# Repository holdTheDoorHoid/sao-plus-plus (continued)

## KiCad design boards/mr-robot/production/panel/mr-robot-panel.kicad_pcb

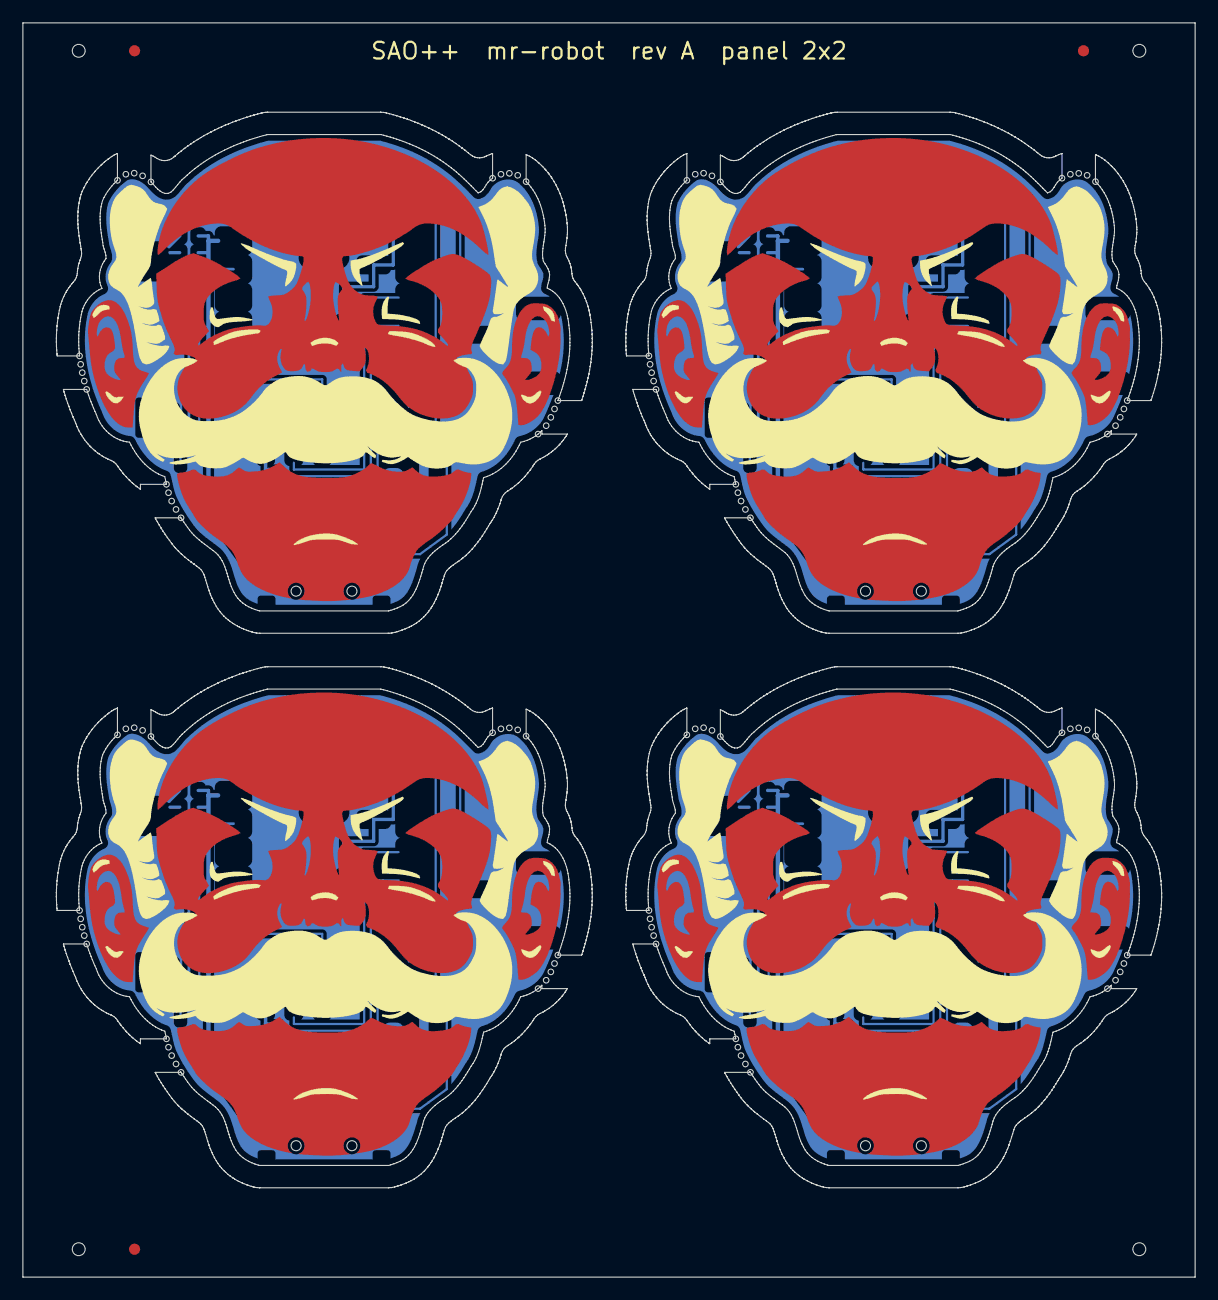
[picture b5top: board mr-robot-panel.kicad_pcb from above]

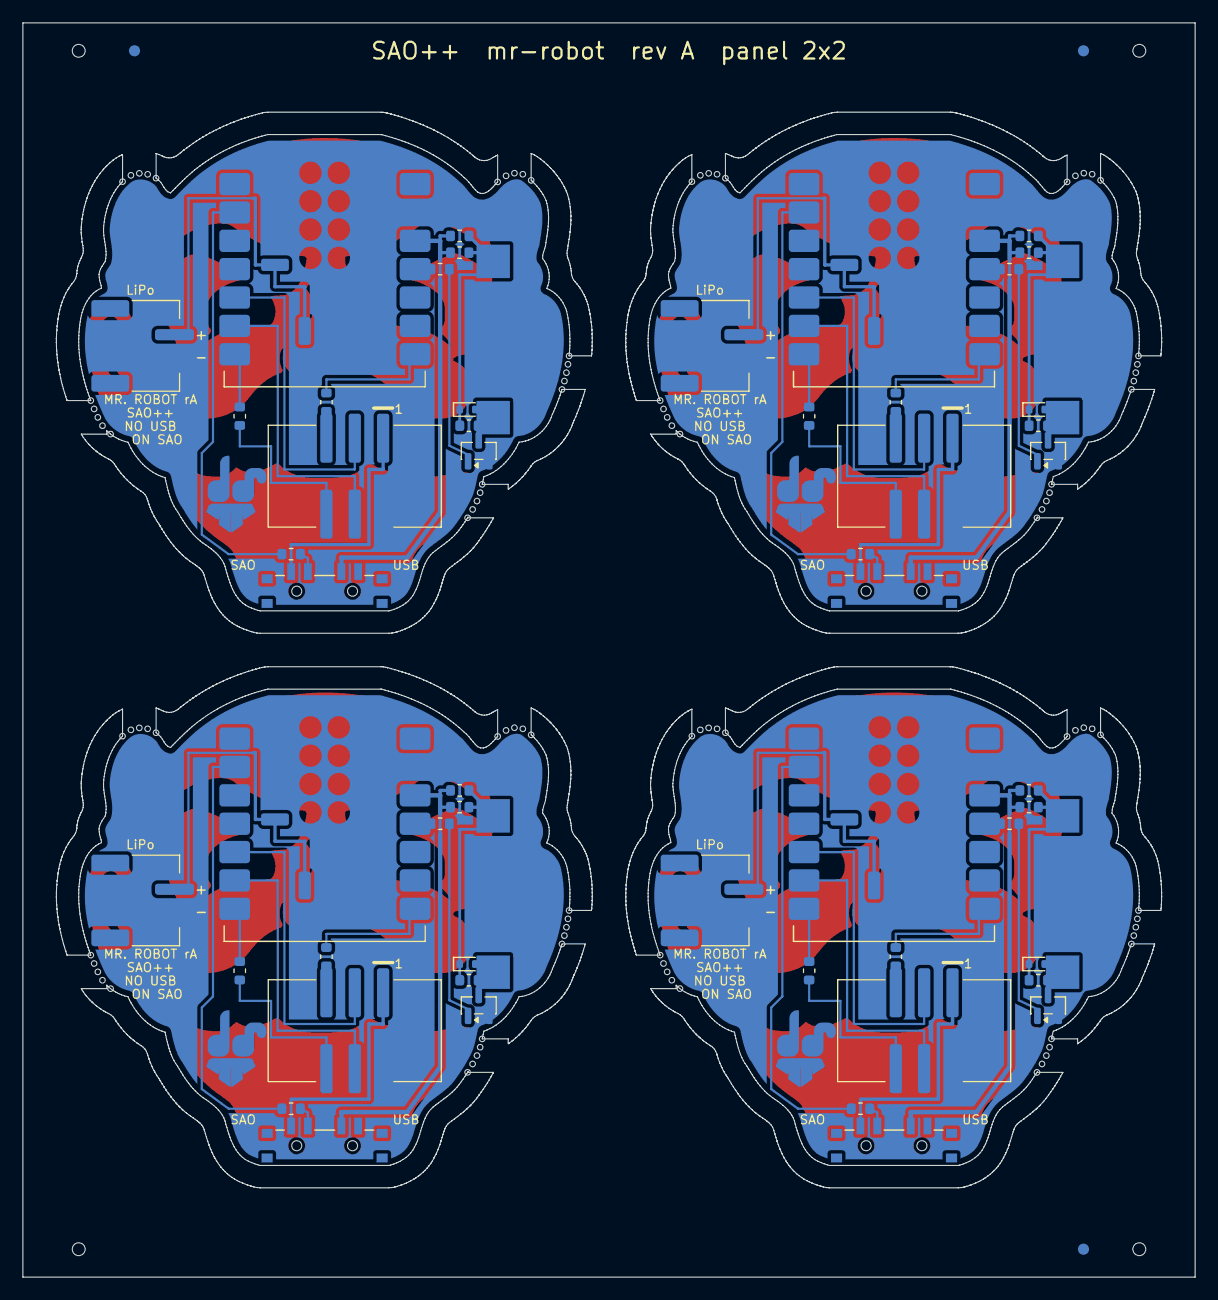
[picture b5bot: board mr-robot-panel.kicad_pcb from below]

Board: 2 copper layers, 105.0 x 112.3 mm, 56 parts (56 on the bottom side), 64 nets.

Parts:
D101, D201, D301, D401: RB751S40; D_SOD-523
J101, J201, J301, J401: SAO v1.69bis; SAOPP_CONN-01_BoxHeader_2x03_P2.54mm_SMD_XFCN_BH254VS-6P
J102, J202, J302, J402: LiPo 3.7 V; SAOPP_CONN-10_JST_PH_S2B-PH-SM4-TB_1x02_Horizontal
LS101, LS201, LS301, LS401: KMTG1102; KMTG-1102
Q101, Q201, Q301, Q401: BC847B; SOT-23
R101, R107, R201, R207, R301, R307, R401, R407: 1.3k; SAOPP_R_0603_1608Metric
R102, R103, R104, R105, R106, R202, R203, R204, R205, R206, R302, R303, R304, R305, R306, R402, R403, R404, R405, R406: 330; SAOPP_R_0603_1608Metric
SW101, SW201, SW301, SW401: SAO / OFF / USB-BAT; SAOPP_SW-01_Slide_SP3T_CK_PCM13SMTR
U101, U201, U301, U401: XIAO ESP32-C3 / S3 / C6; SAOPP_MCU-01_Seeed_XIAO_SMD_C3_S3_C6

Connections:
AUDIO: R101.1, U101.11
B2-AUDIO: R201.1, U201.11
B2-BAT+: J202.1, U201.15
B2-D6_TX: R203.2, U201.7
B2-D7_RX: R202.2, U201.8
B2-GND: J201.2, J202.2, Q201.2, U201.13, U201.16
B2-OFF_SENSE: R204.2, U201.2
B2-OFF_SW: R204.1, SW201.2
B2-Q_BASE: Q201.1, R201.2
B2-SAO_GPIO1: J201.5, R202.1
B2-SAO_GPIO2: J201.6, R203.1
B2-SCL: J201.4, U201.6
B2-SDA: J201.3, U201.5
B2-SPK_MINUS: D201.2, LS201.1, Q201.3, R207.2
B2-SPK_PLUS: D201.1, LS201.2, R205.2, R206.2, R207.1
B2-V3V3: R205.1, R206.1, SW201.3, U201.12
B2-VSAO: J201.1, SW201.1
B3-AUDIO: R301.1, U301.11
B3-BAT+: J302.1, U301.15
B3-D6_TX: R303.2, U301.7
B3-D7_RX: R302.2, U301.8
B3-GND: J301.2, J302.2, Q301.2, U301.13, U301.16
B3-OFF_SENSE: R304.2, U301.2
B3-OFF_SW: R304.1, SW301.2
B3-Q_BASE: Q301.1, R301.2
B3-SAO_GPIO1: J301.5, R302.1
B3-SAO_GPIO2: J301.6, R303.1
B3-SCL: J301.4, U301.6
B3-SDA: J301.3, U301.5
B3-SPK_MINUS: D301.2, LS301.1, Q301.3, R307.2
B3-SPK_PLUS: D301.1, LS301.2, R305.2, R306.2, R307.1
B3-V3V3: R305.1, R306.1, SW301.3, U301.12
B3-VSAO: J301.1, SW301.1
B4-AUDIO: R401.1, U401.11
B4-BAT+: J402.1, U401.15
B4-D6_TX: R403.2, U401.7
B4-D7_RX: R402.2, U401.8
B4-GND: J401.2, J402.2, Q401.2, U401.13, U401.16
B4-OFF_SENSE: R404.2, U401.2
B4-OFF_SW: R404.1, SW401.2
B4-Q_BASE: Q401.1, R401.2
B4-SAO_GPIO1: J401.5, R402.1
B4-SAO_GPIO2: J401.6, R403.1
B4-SCL: J401.4, U401.6
B4-SDA: J401.3, U401.5
B4-SPK_MINUS: D401.2, LS401.1, Q401.3, R407.2
B4-SPK_PLUS: D401.1, LS401.2, R405.2, R406.2, R407.1
B4-V3V3: R405.1, R406.1, SW401.3, U401.12
B4-VSAO: J401.1, SW401.1
BAT+: J102.1, U101.15
D6_TX: R103.2, U101.7
D7_RX: R102.2, U101.8
GND: J101.2, J102.2, Q101.2, U101.13, U101.16
OFF_SENSE: R104.2, U101.2
OFF_SW: R104.1, SW101.2
Q_BASE: Q101.1, R101.2
SAO_GPIO1: J101.5, R102.1
SAO_GPIO2: J101.6, R103.1
SCL: J101.4, U101.6
SDA: J101.3, U101.5
SPK_MINUS: D101.2, LS101.1, Q101.3, R107.2
SPK_PLUS: D101.1, LS101.2, R105.2, R106.2, R107.1
V3V3: R105.1, R106.1, SW101.3, U101.12
VSAO: J101.1, SW101.1

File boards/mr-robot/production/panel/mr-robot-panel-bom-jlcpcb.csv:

Comment,Designator,Footprint,LCSC Part #
RB751S40,"D101,D201,D301,D401",D_SOD-523,C232576
SAO v1.69bis,"J101,J201,J301,J401",SAOPP_CONN-01_BoxHeader_2x03_P2.54mm_SMD_XFCN_BH254VS-6P,C492445
LiPo 3.7 V,"J102,J202,J302,J402",SAOPP_CONN-10_JST_PH_S2B-PH-SM4-TB_1x02_Horizontal,C295747
KMTG1102,"LS101,LS201,LS301,LS401",KMTG-1102,
BC847B,"Q101,Q201,Q301,Q401",SOT-23,C57668
1.3k,"R101,R107,R201,R207,R301,R307,R401,R407",SAOPP_R_0603_1608Metric,C22767
330,"R102,R103,R104,R105,R106,R202,R203,R204,R205,R206,R302,R303,R304,R305,R306,R402,R403,R404,R405,R406",SAOPP_R_0603_1608Metric,C23138
SAO / OFF / USB-BAT,"SW101,SW201,SW301,SW401",SAOPP_SW-01_Slide_SP3T_CK_PCM13SMTR,C221842
XIAO ESP32-C3 / S3 / C6,"U101,U201,U301,U401",SAOPP_MCU-01_Seeed_XIAO_SMD_C3_S3_C6,

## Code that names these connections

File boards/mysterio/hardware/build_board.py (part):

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RCOL = 25.9                                    # R2 / R3 stand upright between the connector and the XIAO
R2_C, R3_C = (RCOL, 42.0), (RCOL, 46.4)
R4_C = (SX + 2.25, SY - 3.2)
r2 = place("R2", R2_C, ("1", (RCOL, R2_C[1] + 0.825)))      # GPIO1 in from below-left, D7 out of the top
r3 = place("R3", R3_C, ("1", (RCOL, R3_C[1] + 0.825)))      # GPIO2 in from below, D6 out of the top; SCL passes between its pads
r4 = place("R4", R4_C, ("1", (R4_C[0] - 0.825, R4_C[1])))   # OFF in on the left, out on the right; badge 3.3 V passes between its pads

# R1 stands on LED D1's own axis, just outside it, so the 3.3 V feed can cross the data line between R1's pads on its
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              (SDA_X, SDA_Y), (SDA_X, u["5"][1]), u["5"]])
# SCL: connector pin 4 -> into the gap -> out on the right -> between R3's pads -> XIAO D5
route("SCL", [j["4"], (j["4"][0], R3_C[1]), (u["6"][0], R3_C[1]), u["6"]])
# GPIO2: connector pin 6 -> R3 (from below) -> D6
route("SAO_GPIO2", [j["6"], (RCOL - 1.2, j["6"][1]), (RCOL, j["6"][1] - 1.2), pp(r3, "1")])
route("D6_TX", [pp(r3, "2"), (RCOL, u["7"][1]), u["7"]])
# GPIO1: connector pin 5 -> R2 (from below) -> under the XIAO's top end -> D7 from above
route("SAO_GPIO1", [j["5"], (RCOL - 1.4, j["5"][1]), (RCOL, j["5"][1] - 0.6 if j["5"][1] - 0.6 > pp(r2, "1")[1] else pp(r2, "1")[1]), pp(r2, "1")])
TOP = YC - 9.95
route("D7_RX", [pp(r2, "2"), (RCOL, TOP), (u["8"][0], TOP), u["8"]])

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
